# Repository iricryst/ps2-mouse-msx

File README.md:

# PS/2 PC Mouse to MSX Mouse Converter

KiCad schematic project for the 2009 Kami Karilov PS/2-to-MSX mouse converter reference design.

Version 2.0

Warning!!! This is still in concept stage. further testing is required. Not ready for production, please test (electrically) before plug in your MSX / Roland.

BOM not available yet
Required parts can be found in the schematic. To keep the pcb clean I removed nearly all markers, deignators and text. 
Please note the pins on the mini-din connector. I removed pin 2 and 6 to make room for traces and let the Vcc plane intact.

Also, the dsub 9 connector should be the female variant ofcourse. I used the male footprint+3Dmodel in Kicad.

And the ATTiny2313 footprint might be incorrect. As far as I know The center pad should not be split in 4 quadrants. Still needs reviewing.

## User manual

This manual is adapted from the original project page by Kamil Karimov (caro):
<https://caro.su/msx/mous4msx.htm>

### What it does

The controller connects to either MSX joystick port and allows an IBM PS/2 mouse
to be used as an MSX mouse or as an MSX joystick. The controller is based on an
Atmel ATTiny2313 running from its internal 8 MHz oscillator.

### Hardware modes

1. Connect the controller to an MSX joystick port and connect a PS/2 mouse.
2. Set the controller switch to `WORK` (contacts 2-3 closed).
3. On power-up, the controller starts in mouse mode and the LED is on.
4. Press the left and right mouse buttons at the same time to switch between
	mouse mode and joystick emulation mode. Repeat the action to switch back.
5. In joystick mode the LED is off. JP2 can be used to select the mouse
	resolution when a modern optical mouse reports movement too quickly.

If the LED flashes approximately once per second, the mouse was not detected.
Check the mouse, its PS/2 compatibility, the PS/2-to-USB adapter if one is
being used, and the controller wiring.

### Programming connection

The controller can be programmed directly from the MSX joystick port. Set the
switch to `PROG` (contacts 1-2 closed) before starting the programmer. The
ATTiny2313 connections are:

| ATTiny2313 | Function | MSX joystick pin/signal |
| ---: | --- | --- |
| 1 | RESET | 8 / STROBE |
| 17 | MOSI | 6 / TrgA |
| 18 | MISO | 1 / Up |
| 19 | SCK | 7 / TrgB |
| 20 | VDD | 5 / +5 V |
| 10 | GND | 9 / GND |

Confirm the pinout and power wiring before applying power. The original design
is experimental and should be electrically tested before connecting it to an
MSX or Roland computer.

### Updating the firmware

The `software` folder contains the original downloads and extracted files:

- `software/msx_ms21/msx_ms21.hex` - firmware version 2.1.
- `software/prg2313t/PRG2313T.COM` - MSX programmer version 0.4.
- `software/prg2313t/prg2313t.src/` - programmer source and build files.

On an MSX, copy `PRG2313T.COM` and the desired Intel-HEX file to an accessible
drive, set the controller to `PROG`, and run:

```text
A>PRG2313T MSX_MS21.HEX
```

The programmer checks for an ATTiny2313, reads its signature, fuse settings and
current firmware, then updates the fuses for the internal 8 MHz oscillator if
needed. If the firmware differs, it writes and verifies the new image and
reports `Ok` or `Error`. Running the command without a HEX filename only
reports the detected controller and its current state.

After programming, power off, return the switch to `WORK`, and reconnect the
mouse. The included programmer documentation describes the original MSX
environment and command behaviour in more detail.

### Download attribution

The files in `software/` were downloaded from the original project page on
2026-09-10. They are retained here for use with this hardware project; the
original author and any notices included with the downloaded files remain the
authoritative source for their licensing and redistribution terms.

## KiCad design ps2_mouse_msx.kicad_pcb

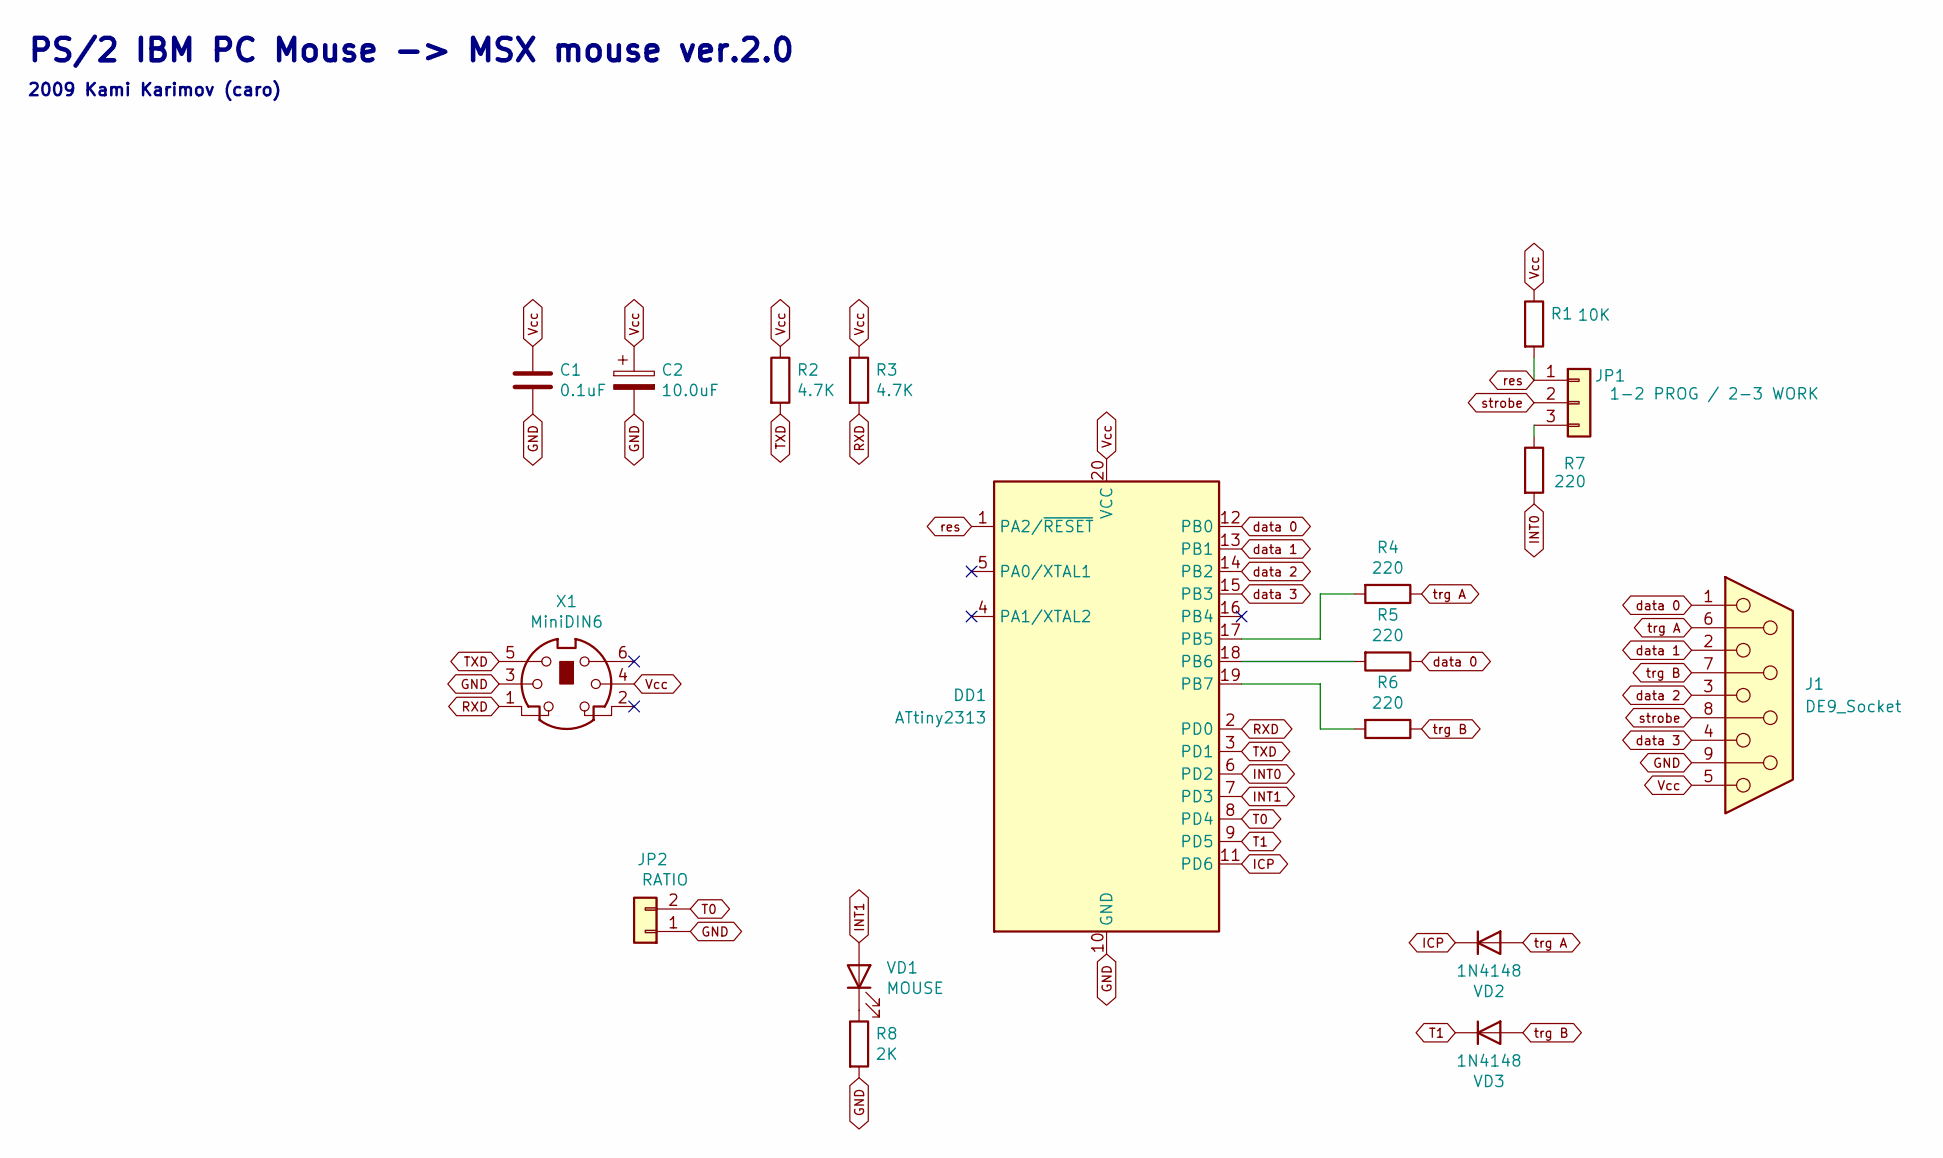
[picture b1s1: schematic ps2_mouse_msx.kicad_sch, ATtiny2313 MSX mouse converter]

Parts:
C1: 0.1uF; C_0402_1005Metric
C2: 10.0uF; C_0402_1005Metric
DD1: ATtiny2313; MLF-20-1EP_4x4mm_P0.5mm_EP2.6x2.6mm
J1: DE9_Socket; DSUB-9_Pins_Horizontal_P2.77x2.84mm_EdgePinOffset4.94mm_Hou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
JP1: 1-2 PROG / 2-3 WORK; PinHeader_1x03_P1.00mm_Vertical
JP2: RATIO; PinHeader_1x02_P1.00mm_Vertical
R1: 10K; R_0402_1005Metric
R2, R3: 4.7K; R_0402_1005Metric
R4, R5, R6, R7: 220; R_0402_1005Metric
R8: 2K; R_0402_1005Metric
VD1: MOUSE; LED_0402_1005Metric
VD2, VD3: 1N4148; D_0402_1005Metric
X1: MiniDIN6; DIN8

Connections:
GND: C1.2, C2.2, DD1.10 (GND), J1.9, JP2.1, R8.2, X1.3
ICP: DD1.11 (PD6), VD2.1 (K)
INT0: DD1.6 (PD2), R7.2
INT1: DD1.7 (PD3), VD1.2 (A)
unnamed: DD1.17 (PB5), R4.2
unnamed: DD1.18 (PB6), R5.2
unnamed: DD1.19 (PB7), R6.2
unnamed: JP1.3, R7.1
unnamed: R8.1, VD1.1 (K)
RXD: DD1.2 (PD0), R3.2, X1.1
T0: DD1.8 (PD4), JP2.2
T1: DD1.9 (PD5), VD3.1 (K)
TXD: DD1.3 (PD1), R2.2, X1.5
Vcc: C1.1, C2.1, DD1.20 (VCC), J1.5, R1.1, R2.1, R3.1, X1.4
data 0: DD1.12 (PB0), J1.1, R5.1
data 1: DD1.13 (PB1), J1.2
data 2: DD1.14 (PB2), J1.3
data 3: DD1.15 (PB3), J1.4
res: DD1.1 (PA2/~RESET), JP1.1, R1.2
strobe: J1.8, JP1.2
trg A: J1.6, R4.1, VD2.2 (A)
trg B: J1.7, R6.1, VD3.2 (A)

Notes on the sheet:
PS/2 IBM PC Mouse -> MSX mouse ver.2.0
2009 Kami Karimov (caro)

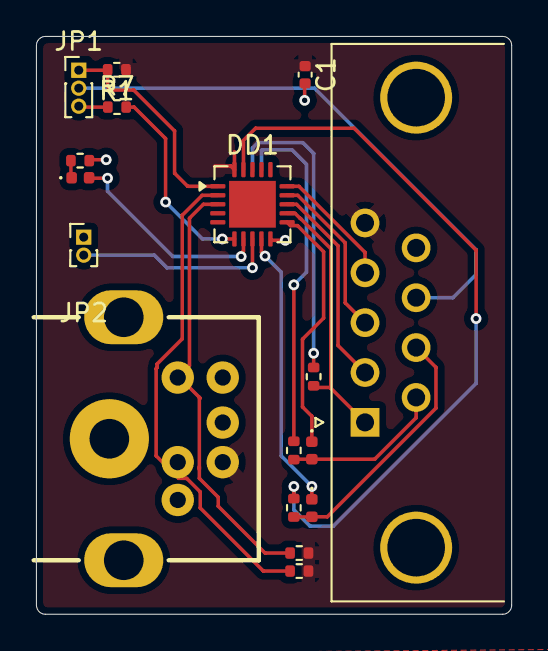
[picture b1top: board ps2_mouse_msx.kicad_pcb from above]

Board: 2 copper layers, 26.4 x 32.1 mm, 17 parts (0 on the bottom side), 22 nets.
